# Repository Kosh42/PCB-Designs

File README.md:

# PCB Designs
 A place to share my KiCAD fumblings

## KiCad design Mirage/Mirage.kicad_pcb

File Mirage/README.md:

<p xmlns:cc="http://creativecommons.org/ns#" xmlns:dct="http://purl.org/dc/terms/"><span property="dct:title">Mirage LED Controller</span> by <span property="cc:attributionName">Kosh42EFG</span> is licensed under <a href="http://creativecommons.org/licenses/by/4.0/?ref=chooser-v1" target="_blank" rel="license noopener noreferrer" style="display:inline-block;">Attribution 4.0 International</a></p>

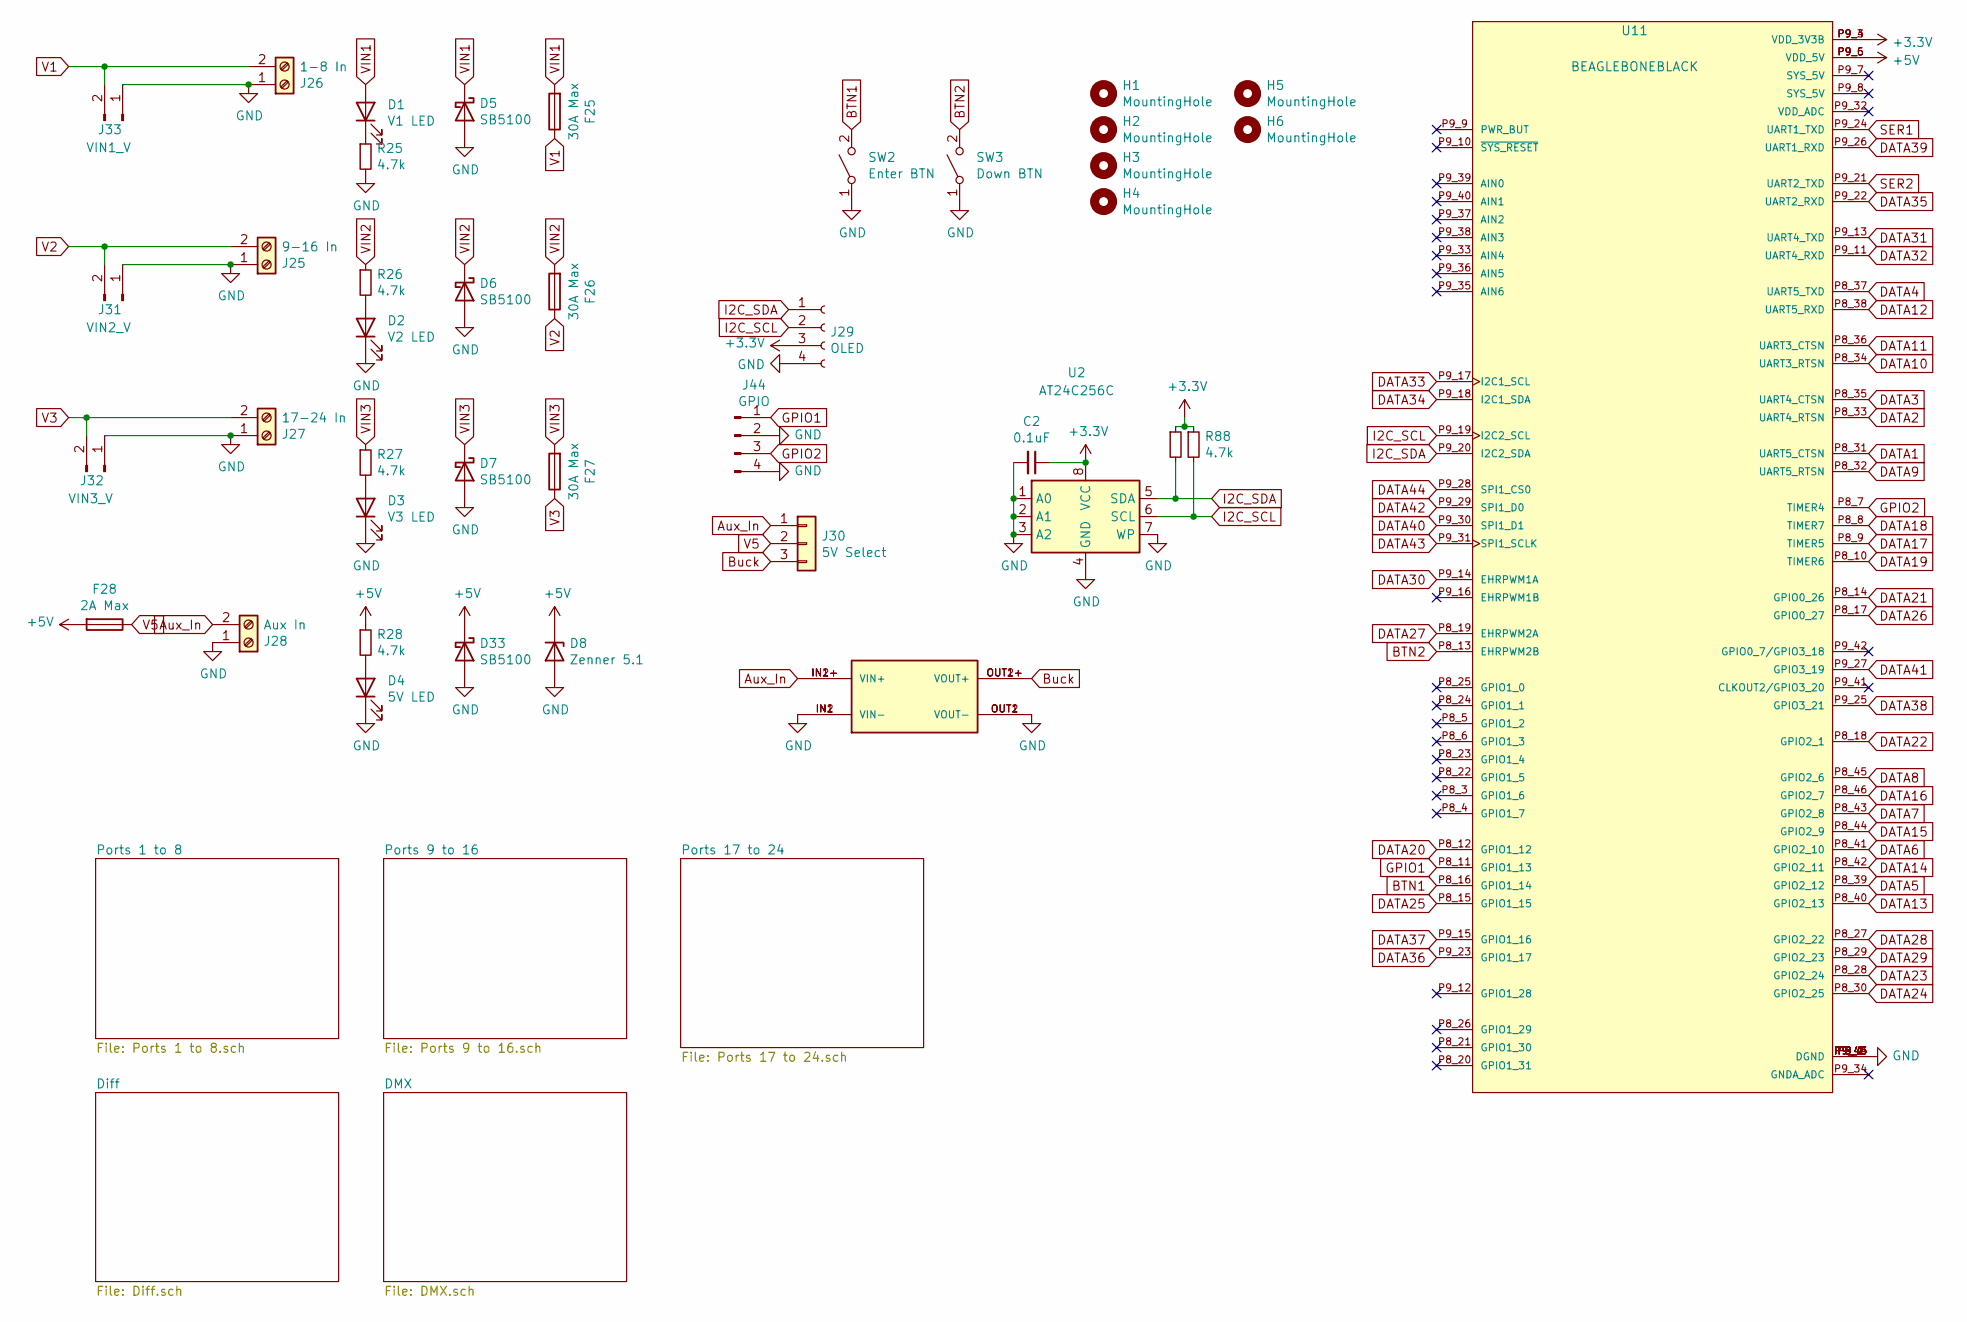
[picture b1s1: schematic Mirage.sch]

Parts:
C2: 0.1uF; C_0805_2012Metric
D1: V1 LED; LED_0603_1608Metric
D2: V2 LED; LED_0603_1608Metric
D3: V3 LED; LED_0603_1608Metric
D4: 5V LED; LED_0603_1608Metric
D5, D6, D7, D33: SB5100; D_DO-201AD_P12.70mm_Horizontal
D8: Zenner 5.1; D_5W_P10.16mm_Horizontal
F25, F26, F27: 30A Max; 3544-2
F28: 2A Max; 3544-2
H1, H2, H3, H4, H5, H6: MountingHole; MountingHole_3.2mm_M3_Pad_TopBottom
J25: 9-16 In; TerminalBlock_MetzConnect_Type701_RT11L02HGLU_1x02_P6.35mm_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
J26: 1-8 In; TerminalBlock_MetzConnect_Type701_RT11L02HGLU_1x02_P6.35mm_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
J27: 17-24 In; TerminalBlock_MetzConnect_Type701_RT11L02HGLU_1x02_P6.35mm_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
J28: Aux In; TerminalBlock_MetzConnect_Type701_RT11L02HGLU_1x02_P6.35mm_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
J29: OLED; PinSocket_1x04_P2.54mm_Vertical
J30: 5V Select; PinHeader_1x03_P2.54mm_Vertical
J31: VIN2_V; JST_XH_B2B-XH-A_1x02_P2.50mm_Vertical
J32: VIN3_V; JST_XH_B2B-XH-A_1x02_P2.50mm_Vertical
J33: VIN1_V; JST_XH_B2B-XH-A_1x02_P2.50mm_Vertical
J44: GPIO; JST_XH_B4B-XH-A_1x04_P2.50mm_Vertical
R25, R26, R27, R28, R29, R88: 4.7k; R_0805_2012Metric
SW2: Enter BTN; SW_PUSH_6mm
SW3: Down BTN; SW_PUSH_6mm
U2: AT24C256C; SOIC-8_3.9x4.9mm_P1.27mm
U10: MP1584; DC-BRICK
U11: BEAGLEBONEBLACK; MODULE_BEAGLEBONEBLACK; PARTREV C

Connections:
+3V3: C2.1, J29.3, R29.1, R88.1, U2.8 (VCC), U11.P9_3 (VDD_3V3B), U11.P9_4 (VDD_3V3B)
+5V: D8.1 (K), D33.1 (K), F28.2, R28.1, U11.P9_5 (VDD_5V), U11.P9_6 (VDD_5V); also elsewhere on the board
Aux_In: J28.2, J30.1, U10.IN1+ (VIN+), U10.IN2+ (VIN+)
BTN1: SW2.2 (B), U11.P8_16 (GPIO1_14)
BTN2: SW3.2 (B), U11.P8_13 (EHRPWM2B)
Buck: J30.3, U10.OUT1+ (VOUT+), U10.OUT2+ (VOUT+)
DATA1: U11.P8_31 (UART5_CTSN); also elsewhere on the board
DATA2: U11.P8_33 (UART4_RTSN); also elsewhere on the board
DATA3: U11.P8_35 (UART4_CTSN); also elsewhere on the board
DATA4: U11.P8_37 (UART5_TXD); also elsewhere on the board
DATA5: U11.P8_39 (GPIO2_12); also elsewhere on the board
DATA6: U11.P8_41 (GPIO2_10); also elsewhere on the board
DATA7: U11.P8_43 (GPIO2_8); also elsewhere on the board
DATA8: U11.P8_45 (GPIO2_6); also elsewhere on the board
DATA9: U11.P8_32 (UART5_RTSN); also elsewhere on the board
DATA10: U11.P8_34 (UART3_RTSN); also elsewhere on the board
DATA11: U11.P8_36 (UART3_CTSN); also elsewhere on the board
DATA12: U11.P8_38 (UART5_RXD); also elsewhere on the board
DATA13: U11.P8_40 (GPIO2_13); also elsewhere on the board
DATA14: U11.P8_42 (GPIO2_11); also elsewhere on the board
DATA15: U11.P8_44 (GPIO2_9); also elsewhere on the board
DATA16: U11.P8_46 (GPIO2_7); also elsewhere on the board
DATA17: U11.P8_9 (TIMER5); also elsewhere on the board
DATA18: U11.P8_8 (TIMER7); also elsewhere on the board
DATA19: U11.P8_10 (TIMER6); also elsewhere on the board
DATA20: U11.P8_12 (GPIO1_12); also elsewhere on the board
DATA21: U11.P8_14 (GPIO0_26); also elsewhere on the board
DATA22: U11.P8_18 (GPIO2_1); also elsewhere on the board
DATA23: U11.P8_28 (GPIO2_24); also elsewhere on the board
DATA24: U11.P8_30 (GPIO2_25); also elsewhere on the board
DATA25: U11.P8_15 (GPIO1_15); also elsewhere on the board
DATA26: U11.P8_17 (GPIO0_27); also elsewhere on the board
DATA27: U11.P8_19 (EHRPWM2A); also elsewhere on the board
DATA28: U11.P8_27 (GPIO2_22); also elsewhere on the board
DATA29: U11.P8_29 (GPIO2_23); also elsewhere on the board
DATA30: U11.P9_14 (EHRPWM1A); also elsewhere on the board
DATA31: U11.P9_13 (UART4_TXD); also elsewhere on the board
DATA32: U11.P9_11 (UART4_RXD); also elsewhere on the board
DATA33: U11.P9_17 (I2C1_SCL); also elsewhere on the board
DATA34: U11.P9_18 (I2C1_SDA); also elsewhere on the board
DATA35: U11.P9_22 (UART2_RXD); also elsewhere on the board
DATA36: U11.P9_23 (GPIO1_17); also elsewhere on the board
DATA37: U11.P9_15 (GPIO1_16); also elsewhere on the board
DATA38: U11.P9_25 (GPIO3_21); also elsewhere on the board
DATA39: U11.P9_26 (UART1_RXD); also elsewhere on the board
DATA40: U11.P9_30 (SPI1_D1); also elsewhere on the board
DATA41: U11.P9_27 (GPIO3_19); also elsewhere on the board
DATA42: U11.P9_29 (SPI1_D0); also elsewhere on the board
DATA43: U11.P9_31 (SPI1_SCLK); also elsewhere on the board
DATA44: U11.P9_28 (SPI1_CS0); also elsewhere on the board
GND: C2.2, D2.1 (K), D3.1 (K), D4.1 (K), D5.2 (A), D6.2 (A), D7.2 (A), D8.2 (A), D33.2 (A), J25.1, J26.1, J27.1, J28.1, J29.4, J31.1, J32.1, J33.1, J44.2, J44.4, R25.2, SW2.1 (A), SW3.1 (A), U2.1 (A0), U2.2 (A1), U2.3 (A2), U2.4 (GND), U2.7 (WP), U10.IN1 (VIN-), U10.IN2 (VIN-), U10.OUT1 (VOUT-), U10.OUT2 (VOUT-), U11.P8_1 (DGND), U11.P8_2 (DGND), U11.P9_1 (DGND), U11.P9_2 (DGND), U11.P9_43 (DGND), U11.P9_44 (DGND), U11.P9_45 (DGND), U11.P9_46 (DGND); also elsewhere on the board
GPIO1: J44.1, U11.P8_11 (GPIO1_13)
GPIO2: J44.3, U11.P8_7 (TIMER4)
I2C_SCL: J29.2, R88.2, U2.6 (SCL), U11.P9_19 (I2C2_SCL)
I2C_SDA: J29.1, R29.2, U2.5 (SDA), U11.P9_20 (I2C2_SDA)
unnamed: D1.1 (K), R25.1
unnamed: D2.2 (A), R26.2
unnamed: D3.2 (A), R27.2
unnamed: D4.2 (A), R28.2
SER1: U11.P9_24 (UART1_TXD); also elsewhere on the board
SER2: U11.P9_21 (UART2_TXD); also elsewhere on the board
V1: F25.1, J26.2, J33.2
V2: F26.1, J25.2, J31.2
V3: F27.1, J27.2, J32.2
V5: F28.1, J30.2
VIN1: D1.2 (A), D5.1 (K), F25.2; also elsewhere on the board
VIN2: D6.1 (K), F26.2, R26.1; also elsewhere on the board
VIN3: D7.1 (K), F27.2, R27.1; also elsewhere on the board

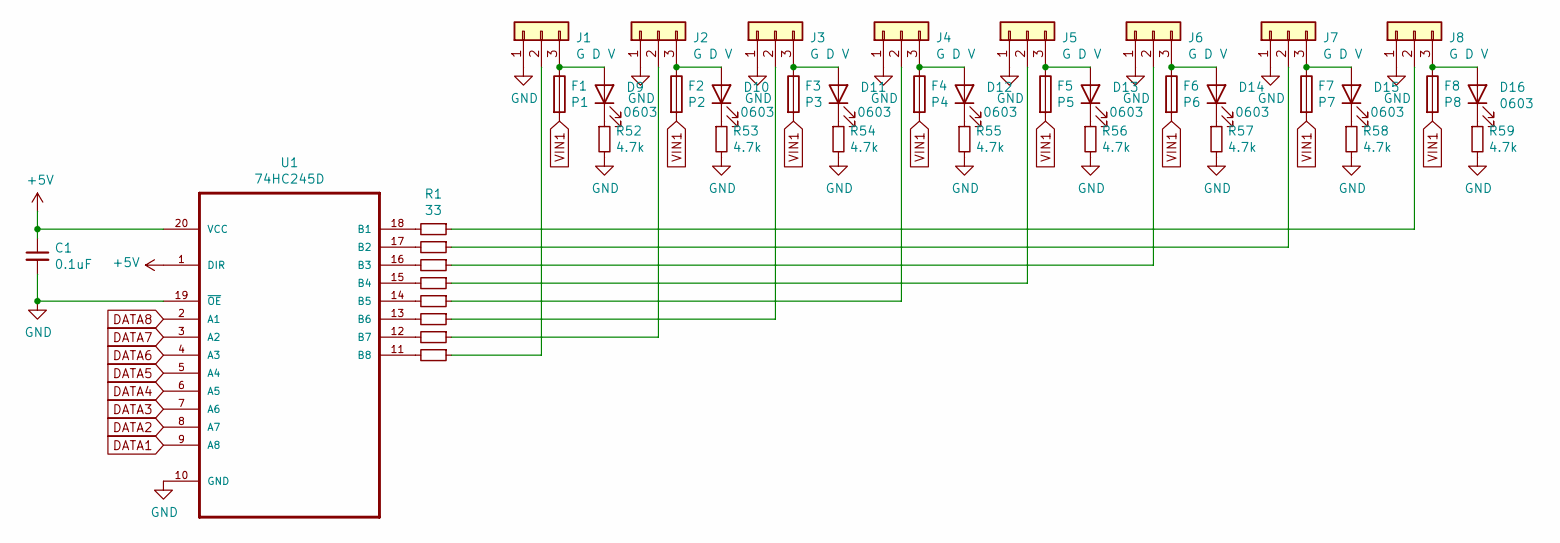
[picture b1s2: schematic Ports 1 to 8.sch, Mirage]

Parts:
C1: 0.1uF; C_0805_2012Metric
D9, D10, D11, D12, D13, D14, D15, D16: 0603; LED_0603_1608Metric
F1: P1; 3544-2
F2: P2; 3544-2
F3: P3; 3544-2
F4: P4; 3544-2
F5: P5; 3544-2
F6: P6; 3544-2
F7: P7; 3544-2
F8: P8; 3544-2
J1, J2, J3, J4, J5, J6, J7, J8: G D V; PhoenixContact_MCV_1,5_3-G-3.5_1x03_P3.50mm_Vertical_Tim
R1, R2, R3, R4, R5, R6, R7, R8: 33; R_0805_2012Metric
R52, R53, R54, R55, R56, R57, R58, R59: 4.7k; R_0805_2012Metric
U1: 74HC245D; SOIC-20W_7.5x12.8mm_P1.27mm

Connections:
+5V: C1.1, U1.1 (DIR), U1.20 (VCC); also elsewhere on the board
DATA1: U1.9 (A8); also elsewhere on the board
DATA2: U1.8 (A7); also elsewhere on the board
DATA3: U1.7 (A6); also elsewhere on the board
DATA4: U1.6 (A5); also elsewhere on the board
DATA5: U1.5 (A4); also elsewhere on the board
DATA6: U1.4 (A3); also elsewhere on the board
DATA7: U1.3 (A2); also elsewhere on the board
DATA8: U1.2 (A1); also elsewhere on the board
GND: C1.2, J1.1, J2.1, J3.1, J4.1, J5.1, J6.1, J7.1, J8.1, R52.2, R53.2, R54.2, R55.2, R56.2, R57.2, R58.2, R59.2, U1.10 (GND), U1.19 (~OE); also elsewhere on the board
unnamed: D9.1 (K), R52.1
unnamed: D9.2 (A), F1.1, J1.3
unnamed: D10.1 (K), R53.1
unnamed: D10.2 (A), F2.1, J2.3
unnamed: D11.1 (K), R54.1
unnamed: D11.2 (A), F3.1, J3.3
unnamed: D12.1 (K), R55.1
unnamed: D12.2 (A), F4.1, J4.3
unnamed: D13.1 (K), R56.1
unnamed: D13.2 (A), F5.1, J5.3
unnamed: D14.1 (K), R57.1
unnamed: D14.2 (A), F6.1, J6.3
unnamed: D15.1 (K), R58.1
unnamed: D15.2 (A), F7.1, J7.3
unnamed: D16.1 (K), R59.1
unnamed: D16.2 (A), F8.1, J8.3
unnamed: J1.2, R8.1
unnamed: J2.2, R7.1
unnamed: J3.2, R6.1
unnamed: J4.2, R5.1
unnamed: J5.2, R4.1
unnamed: J6.2, R3.1
unnamed: J7.2, R2.1
unnamed: J8.2, R1.1
unnamed: R1.2, U1.18 (B1)
unnamed: R2.2, U1.17 (B2)
unnamed: R3.2, U1.16 (B3)
unnamed: R4.2, U1.15 (B4)
unnamed: R5.2, U1.14 (B5)
unnamed: R6.2, U1.13 (B6)
unnamed: R7.2, U1.12 (B7)
unnamed: R8.2, U1.11 (B8)
VIN1: F1.2, F2.2, F3.2, F4.2, F5.2, F6.2, F7.2, F8.2; also elsewhere on the board

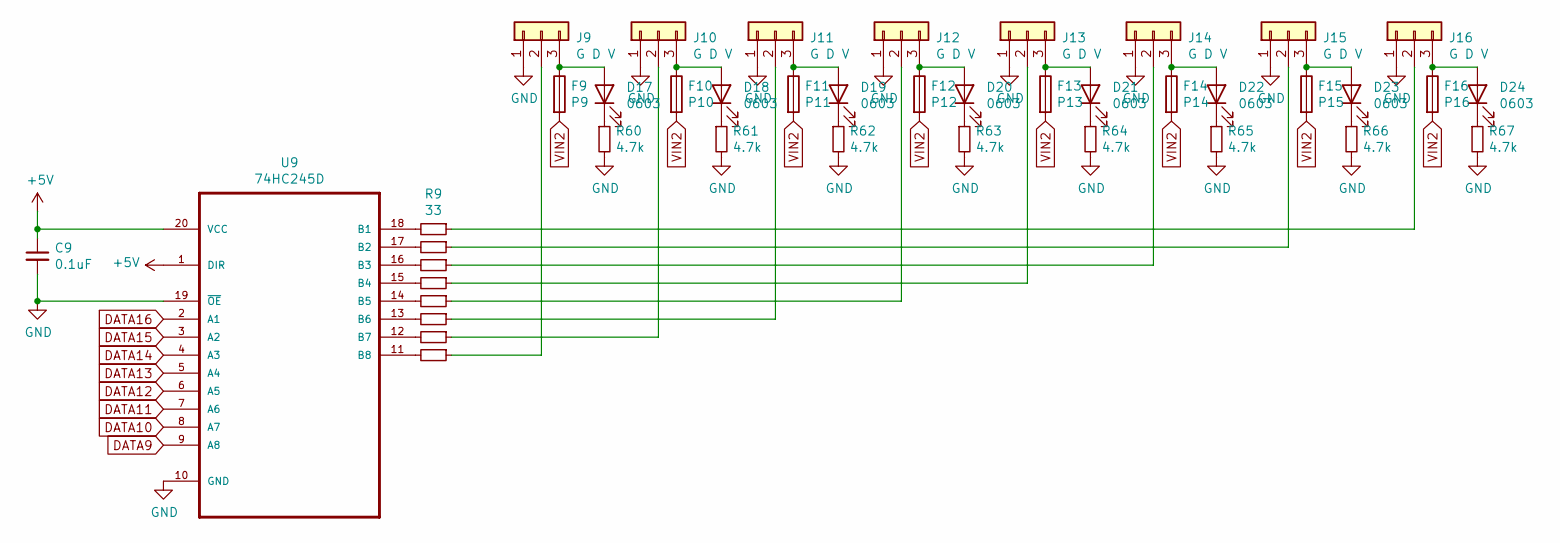
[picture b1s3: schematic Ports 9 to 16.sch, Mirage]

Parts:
C9: 0.1uF; C_0805_2012Metric
D17, D18, D19, D20, D21, D22, D23, D24: 0603; LED_0603_1608Metric
F9: P9; 3544-2
F10: P10; 3544-2
F11: P11; 3544-2
F12: P12; 3544-2
F13: P13; 3544-2
F14: P14; 3544-2
F15: P15; 3544-2
F16: P16; 3544-2
J9, J10, J11, J12, J13, J14, J15, J16: G D V; PhoenixContact_MCV_1,5_3-G-3.5_1x03_P3.50mm_Vertical_Tim
R9, R10, R11, R12, R13, R14, R15, R16: 33; R_0805_2012Metric
R60, R61, R62, R63, R64, R65, R66, R67: 4.7k; R_0805_2012Metric
U9: 74HC245D; SOIC-20W_7.5x12.8mm_P1.27mm

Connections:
+5V: C9.1, U9.1 (DIR), U9.20 (VCC); also elsewhere on the board
DATA9: U9.9 (A8); also elsewhere on the board
DATA10: U9.8 (A7); also elsewhere on the board
DATA11: U9.7 (A6); also elsewhere on the board
DATA12: U9.6 (A5); also elsewhere on the board
DATA13: U9.5 (A4); also elsewhere on the board
DATA14: U9.4 (A3); also elsewhere on the board
DATA15: U9.3 (A2); also elsewhere on the board
DATA16: U9.2 (A1); also elsewhere on the board
GND: C9.2, J9.1, J10.1, J11.1, J12.1, J13.1, J14.1, J15.1, J16.1, R60.2, R61.2, R62.2, R63.2, R64.2, R65.2, R66.2, R67.2, U9.10 (GND), U9.19 (~OE); also elsewhere on the board
unnamed: D17.1 (K), R60.1
unnamed: D17.2 (A), F9.1, J9.3
unnamed: D18.1 (K), R61.1
unnamed: D18.2 (A), F10.1, J10.3
unnamed: D19.1 (K), R62.1
unnamed: D19.2 (A), F11.1, J11.3
unnamed: D20.1 (K), R63.1
unnamed: D20.2 (A), F12.1, J12.3
unnamed: D21.1 (K), R64.1
unnamed: D21.2 (A), F13.1, J13.3
unnamed: D22.1 (K), R65.1
unnamed: D22.2 (A), F14.1, J14.3
unnamed: D23.1 (K), R66.1
unnamed: D23.2 (A), F15.1, J15.3
unnamed: D24.1 (K), R67.1
unnamed: D24.2 (A), F16.1, J16.3
unnamed: J9.2, R16.1
unnamed: J10.2, R15.1
unnamed: J11.2, R14.1
unnamed: J12.2, R13.1
unnamed: J13.2, R12.1
unnamed: J14.2, R11.1
unnamed: J15.2, R10.1
unnamed: J16.2, R9.1
unnamed: R9.2, U9.18 (B1)
unnamed: R10.2, U9.17 (B2)
unnamed: R11.2, U9.16 (B3)
unnamed: R12.2, U9.15 (B4)
unnamed: R13.2, U9.14 (B5)
unnamed: R14.2, U9.13 (B6)
unnamed: R15.2, U9.12 (B7)
unnamed: R16.2, U9.11 (B8)
VIN2: F9.2, F10.2, F11.2, F12.2, F13.2, F14.2, F15.2, F16.2; also elsewhere on the board

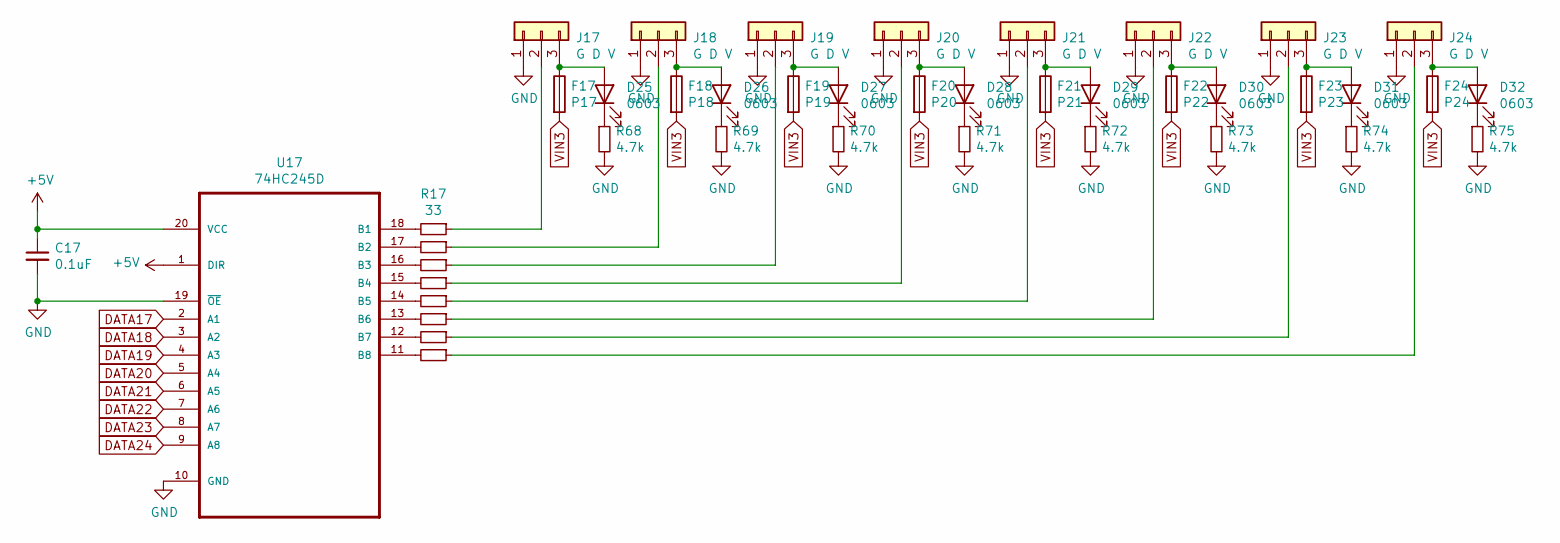
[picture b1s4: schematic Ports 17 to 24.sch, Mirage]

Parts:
C17: 0.1uF; C_0805_2012Metric
D25, D26, D27, D28, D29, D30, D31, D32: 0603; LED_0603_1608Metric
F17: P17; 3544-2
F18: P18; 3544-2
F19: P19; 3544-2
F20: P20; 3544-2
F21: P21; 3544-2
F22: P22; 3544-2
F23: P23; 3544-2
F24: P24; 3544-2
J17, J18, J19, J20, J21, J22, J23, J24: G D V; PhoenixContact_MCV_1,5_3-G-3.5_1x03_P3.50mm_Vertical_Tim
R17, R18, R19, R20, R21, R22, R23, R24: 33; R_0805_2012Metric
R68, R69, R70, R71, R72, R73, R74, R75: 4.7k; R_0805_2012Metric
U17: 74HC245D; SOIC-20W_7.5x12.8mm_P1.27mm

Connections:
+5V: C17.1, U17.1 (DIR), U17.20 (VCC); also elsewhere on the board
DATA17: U17.2 (A1); also elsewhere on the board
DATA18: U17.3 (A2); also elsewhere on the board
DATA19: U17.4 (A3); also elsewhere on the board
DATA20: U17.5 (A4); also elsewhere on the board
DATA21: U17.6 (A5); also elsewhere on the board
DATA22: U17.7 (A6); also elsewhere on the board
DATA23: U17.8 (A7); also elsewhere on the board
DATA24: U17.9 (A8); also elsewhere on the board
GND: C17.2, J17.1, J18.1, J19.1, J20.1, J21.1, J22.1, J23.1, J24.1, R68.2, R69.2, R70.2, R71.2, R72.2, R73.2, R74.2, R75.2, U17.10 (GND), U17.19 (~OE); also elsewhere on the board
unnamed: D25.1 (K), R68.1
unnamed: D25.2 (A), F17.1, J17.3
unnamed: D26.1 (K), R69.1
unnamed: D26.2 (A), F18.1, J18.3
unnamed: D27.1 (K), R70.1
unnamed: D27.2 (A), F19.1, J19.3
unnamed: D28.1 (K), R71.1
unnamed: D28.2 (A), F20.1, J20.3
unnamed: D29.1 (K), R72.1
unnamed: D29.2 (A), F21.1, J21.3
unnamed: D30.1 (K), R73.1
unnamed: D30.2 (A), F22.1, J22.3
unnamed: D31.1 (K), R74.1
unnamed: D31.2 (A), F23.1, J23.3
unnamed: D32.1 (K), R75.1
unnamed: D32.2 (A), F24.1, J24.3
unnamed: J17.2, R17.1
unnamed: J18.2, R18.1
unnamed: J19.2, R19.1
unnamed: J20.2, R20.1
unnamed: J21.2, R21.1
unnamed: J22.2, R22.1
unnamed: J23.2, R23.1
unnamed: J24.2, R24.1
unnamed: R17.2, U17.18 (B1)
unnamed: R18.2, U17.17 (B2)
unnamed: R19.2, U17.16 (B3)
unnamed: R20.2, U17.15 (B4)
unnamed: R21.2, U17.14 (B5)
unnamed: R22.2, U17.13 (B6)
unnamed: R23.2, U17.12 (B7)
unnamed: R24.2, U17.11 (B8)
VIN3: F17.2, F18.2, F19.2, F20.2, F21.2, F22.2, F23.2, F24.2; also elsewhere on the board

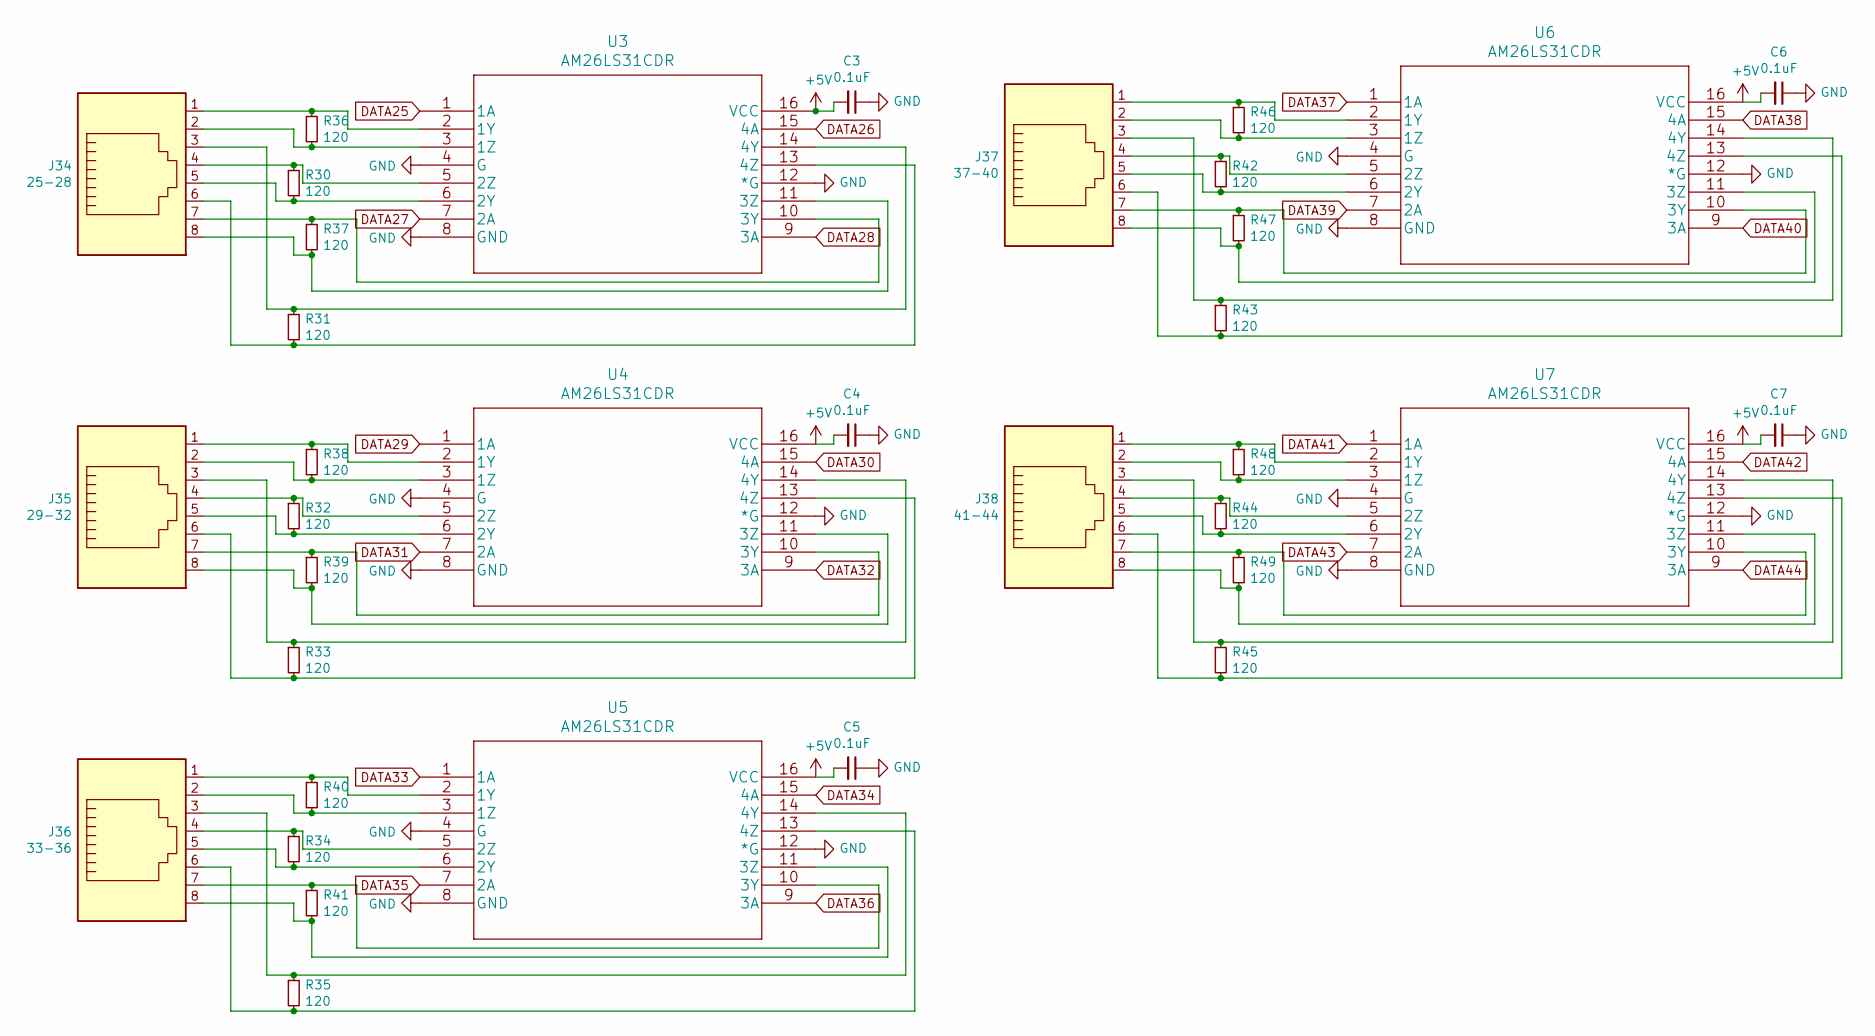
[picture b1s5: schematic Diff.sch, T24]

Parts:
C3, C4, C5, C6, C7: 0.1uF; C_0805_2012Metric
J34: 25-28; RJ45_OST_PJ012-8P8CX_Vertical
J35: 29-32; RJ45_OST_PJ012-8P8CX_Vertical
J36: 33-36; RJ45_OST_PJ012-8P8CX_Vertical
J37: 37-40; RJ45_OST_PJ012-8P8CX_Vertical
J38: 41-44; RJ45_OST_PJ012-8P8CX_Vertical
R30, R31, R32, R33, R34, R35, R36, R37, R38, R39, R40, R41, R42, R43, R44, R45, R46, R47, R48, R49: 120; R_0805_2012Metric
U3, U4, U5, U6, U7: AM26LS31CDR; SOIC-16_3.9x9.9mm_P1.27mm

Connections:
+5V: C3.2, C4.2, C5.2, C6.2, C7.2, U3.16 (VCC), U4.16 (VCC), U5.16 (VCC), U6.16 (VCC), U7.16 (VCC); also elsewhere on the board
DATA25: U3.1 (1A); also elsewhere on the board
DATA26: U3.15 (4A); also elsewhere on the board
DATA27: U3.7 (2A); also elsewhere on the board
DATA28: U3.9 (3A); also elsewhere on the board
DATA29: U4.1 (1A); also elsewhere on the board
DATA30: U4.15 (4A); also elsewhere on the board
DATA31: U4.7 (2A); also elsewhere on the board
DATA32: U4.9 (3A); also elsewhere on the board
DATA33: U5.1 (1A); also elsewhere on the board
DATA34: U5.15 (4A); also elsewhere on the board
DATA35: U5.7 (2A); also elsewhere on the board
DATA36: U5.9 (3A); also elsewhere on the board
DATA37: U6.1 (1A); also elsewhere on the board
DATA38: U6.15 (4A); also elsewhere on the board
DATA39: U6.7 (2A); also elsewhere on the board
DATA40: U6.9 (3A); also elsewhere on the board
DATA41: U7.1 (1A); also elsewhere on the board
DATA42: U7.15 (4A); also elsewhere on the board
DATA43: U7.7 (2A); also elsewhere on the board
DATA44: U7.9 (3A); also elsewhere on the board
GND: C3.1, C4.1, C5.1, C6.1, C7.1, U3.4 (G), U3.8 (GND), U3.12 (*G), U4.4 (G), U4.8 (GND), U4.12 (*G), U5.4 (G), U5.8 (GND), U5.12 (*G), U6.4 (G), U6.8 (GND), U6.12 (*G), U7.4 (G), U7.8 (GND), U7.12 (*G); also elsewhere on the board
unnamed: J34.1, R36.1, U3.2 (1Y)
unnamed: J34.2, R36.2, U3.3 (1Z)
unnamed: J34.3, R31.1, U3.14 (4Y)
unnamed: J34.4, R30.1, U3.5 (2Z)
unnamed: J34.5, R30.2, U3.6 (2Y)
unnamed: J34.6, R31.2, U3.13 (4Z)
unnamed: J34.7, R37.1, U3.10 (3Y)
unnamed: J34.8, R37.2, U3.11 (3Z)
unnamed: J35.1, R38.1, U4.2 (1Y)
unnamed: J35.2, R38.2, U4.3 (1Z)
unnamed: J35.3, R33.1, U4.14 (4Y)
unnamed: J35.4, R32.1, U4.5 (2Z)
unnamed: J35.5, R32.2, U4.6 (2Y)
unnamed: J35.6, R33.2, U4.13 (4Z)
unnamed: J35.7, R39.1, U4.10 (3Y)
unnamed: J35.8, R39.2, U4.11 (3Z)
unnamed: J36.1, R40.1, U5.2 (1Y)
unnamed: J36.2, R40.2, U5.3 (1Z)
unnamed: J36.3, R35.1, U5.14 (4Y)
unnamed: J36.4, R34.1, U5.5 (2Z)
unnamed: J36.5, R34.2, U5.6 (2Y)
unnamed: J36.6, R35.2, U5.13 (4Z)
unnamed: J36.7, R41.1, U5.10 (3Y)
unnamed: J36.8, R41.2, U5.11 (3Z)
unnamed: J37.1, R46.1, U6.2 (1Y)
unnamed: J37.2, R46.2, U6.3 (1Z)
unnamed: J37.3, R43.1, U6.14 (4Y)
unnamed: J37.4, R42.1, U6.5 (2Z)
unnamed: J37.5, R42.2, U6.6 (2Y)
unnamed: J37.6, R43.2, U6.13 (4Z)
unnamed: J37.7, R47.1, U6.10 (3Y)
unnamed: J37.8, R47.2, U6.11 (3Z)
unnamed: J38.1, R48.1, U7.2 (1Y)
unnamed: J38.2, R48.2, U7.3 (1Z)
unnamed: J38.3, R45.1, U7.14 (4Y)
unnamed: J38.4, R44.1, U7.5 (2Z)
unnamed: J38.5, R44.2, U7.6 (2Y)
unnamed: J38.6, R45.2, U7.13 (4Z)
unnamed: J38.7, R49.1, U7.10 (3Y)
unnamed: J38.8, R49.2, U7.11 (3Z)

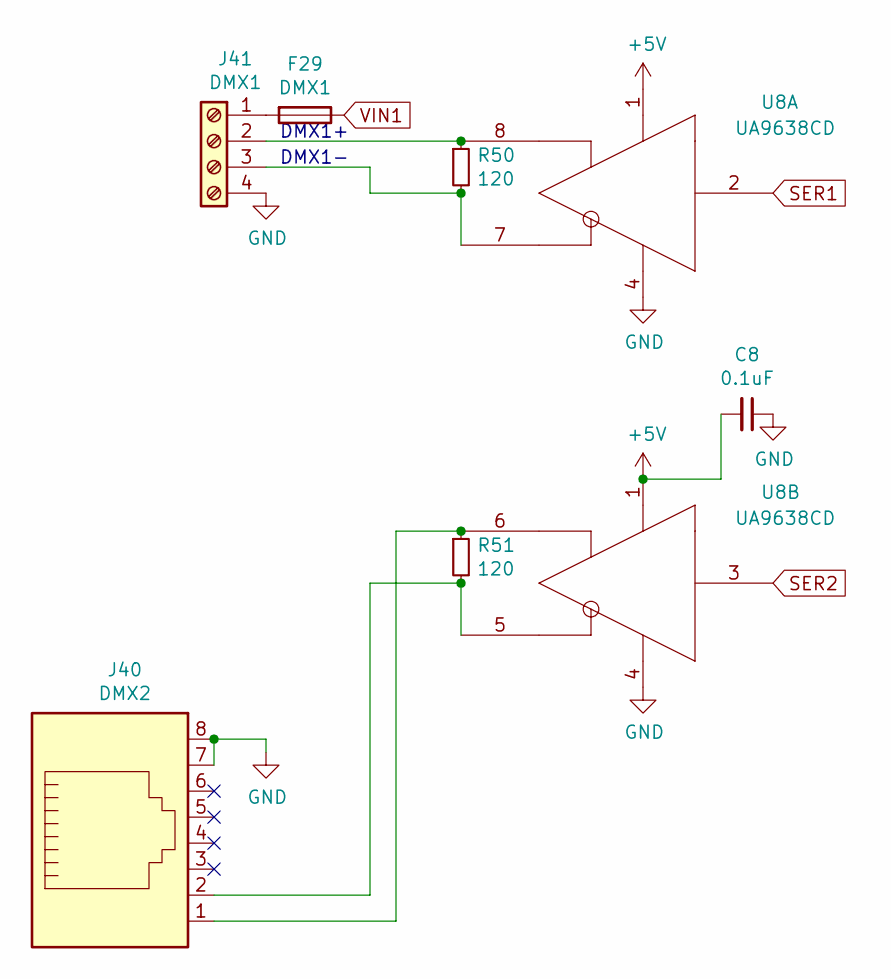
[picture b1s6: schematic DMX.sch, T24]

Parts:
C8: 0.1uF; C_0805_2012Metric
F29: DMX1; 3544-2
J40: DMX2; RJ45_OST_PJ012-8P8CX_Vertical
J41: DMX1; PhoenixContact_MCV_1,5_4-G-3.5_1x04_P3.50mm_Vertical
R50, R51: 120; R_0805_2012Metric
U8: UA9638CD; SOIC-8_3.9x4.9mm_P1.27mm

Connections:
+5V: C8.2, U8.1 (VCC); also elsewhere on the board
GND: C8.1, J40.7, J40.8, J41.4, U8.4 (GND); also elsewhere on the board
unnamed: F29.2, J41.1
unnamed: J40.1, R51.1, U8.6 (OUTB)
unnamed: J40.2, R51.2, U8.5 (OUTA)
unnamed: J41.2, R50.1, U8.8 (OUTB)
unnamed: J41.3, R50.2, U8.7 (OUTA)
SER1: U8.2 (IN); also elsewhere on the board
SER2: U8.3 (IN); also elsewhere on the board
VIN1: F29.1; also elsewhere on the board

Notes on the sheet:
DMX1+
DMX1-

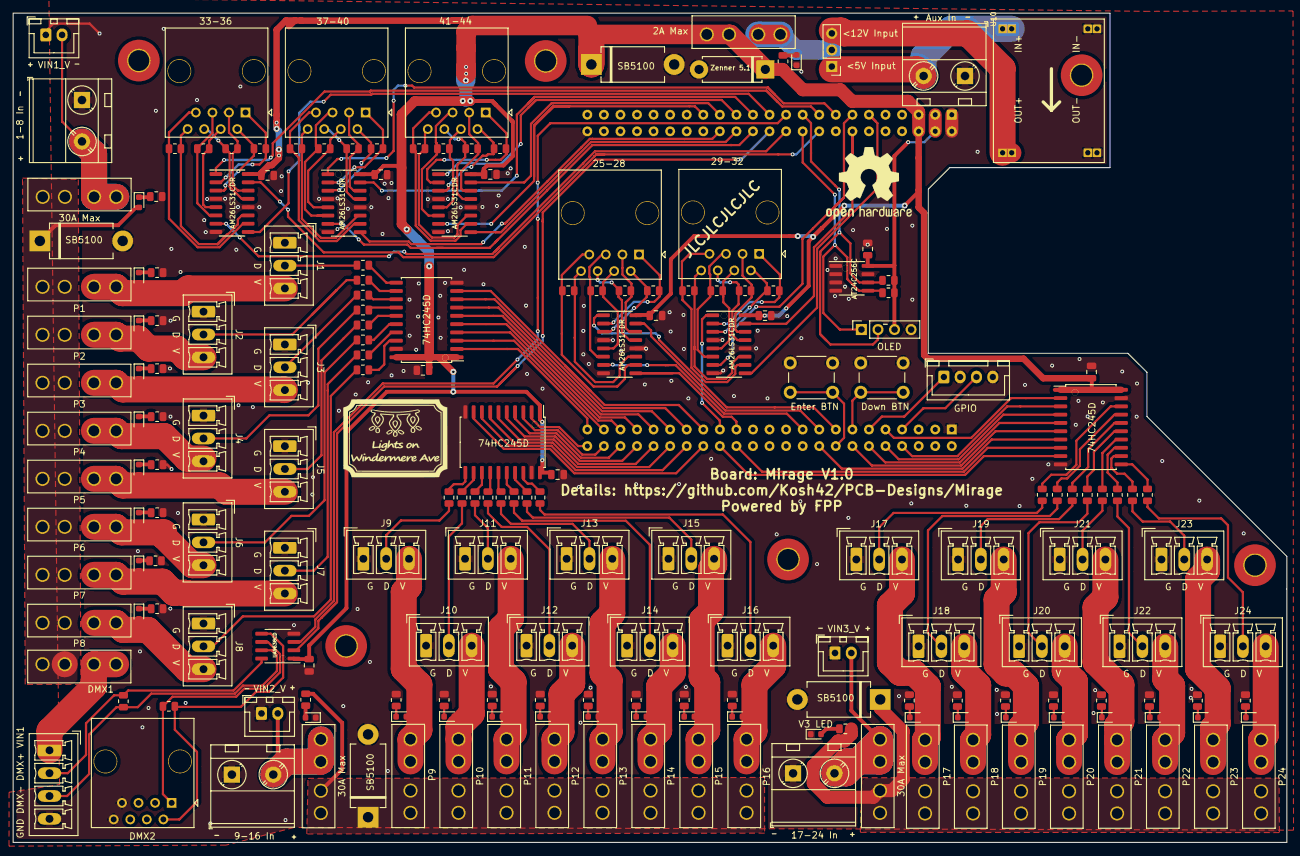
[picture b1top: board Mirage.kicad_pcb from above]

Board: 2 copper layers, 195.3 x 127.1 mm, 209 parts (0 on the bottom side), 209 nets.

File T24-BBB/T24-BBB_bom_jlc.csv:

"Comment","Designator","Footprint","LCSC Part #"
"0.1uF","C2,C1,C9,C17,C3,C4,C5,C7,C6,C8","C_0805_2012Metric","C49678"
"V1 LED","D1","LED_0603_1608Metric","C72043"
"V2 LED","D2","LED_0603_1608Metric","C72043"
"V3 LED","D3","LED_0603_1608Metric","C72043"
"5V LED","D4","LED_0603_1608Metric","C72043"
"0603","D16,D15,D14,D13,D12,D11,D10,D9,D24,D23,D22,D21,D20,D19,D18,D17,D32,D31,D30,D29,D28,D27,D26,D25","LED_0603_1608Metric","C72043"
"33","R1,R2,R3,R4,R5,R6,R7,R8,R9,R10,R11,R12,R13,R14,R15,R16,R17,R18,R19,R20,R21,R22,R23,R24","R_0805_2012Metric","C17634"
"4.7k","R25,R26,R28,R27,R88,R29,R59,R58,R57,R56,R55,R54,R53,R52,R67,R66,R65,R64,R63,R62,R61,R60,R75,R74,R73,R72,R71,R70,R69,R68","R_0805_2012Metric","C17673"
"120","R30,R36,R37,R31,R32,R38,R39,R33,R34,R40,R41,R35,R42,R46,R47,R43,R44,R48,R49,R45,R50,R51","R_0805_2012Metric","C17437"
"74HC245D","U1,U9,U17","SOIC-20W_7.5x12.8mm_P1.27mm","C5625"
"AT24C256C","U2","SOIC-8_3.9x4.9mm_P1.27mm","C6482"
"AM26LS31CDR","U3,U4,U5,U6,U7","SOIC-16_3.9x9.9mm_P1.27mm","C6179"
"UA9638CD","U8","SOIC-8_3.9x4.9mm_P1.27mm","C435812"

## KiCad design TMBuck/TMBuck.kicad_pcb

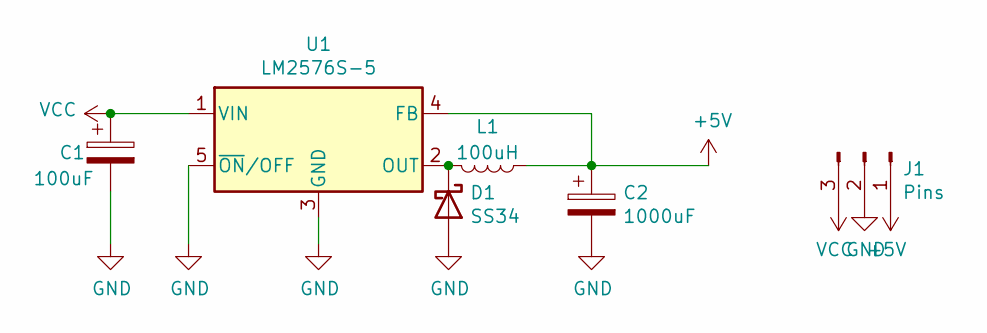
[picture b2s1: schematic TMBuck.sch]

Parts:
C1: 100uF; CP_Radial_D5.0mm_P2.00mm
C2: 1000uF; CP_Radial_D10.0mm_P5.00mm
D1: SS34; D_SMA; LCSC C8678
J1: Pins; PinHeader_1x03_P2.54mm_Horizontal
L1: 100uH; L_0805_2012Metric; LCSC C68035
U1: LM2576S-5; TO-263-5_TabPin3; LCSC C340927

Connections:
+5V: C2.1, J1.1, L1.1, U1.4 (FB)
GND: C1.2, C2.2, D1.2 (A), J1.2, U1.3 (GND), U1.5 (~ON~/OFF)
unnamed: D1.1 (K), L1.2, U1.2 (OUT)
VCC: C1.1, J1.3, U1.1 (VIN)

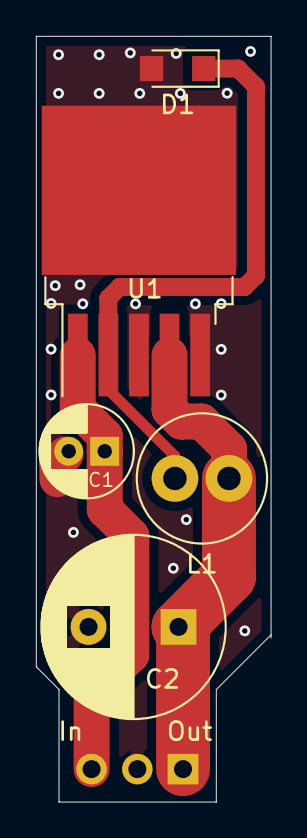
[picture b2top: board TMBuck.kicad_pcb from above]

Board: 2 copper layers, 13.0 x 42.5 mm, 6 parts (1 on the bottom side), 4 nets.

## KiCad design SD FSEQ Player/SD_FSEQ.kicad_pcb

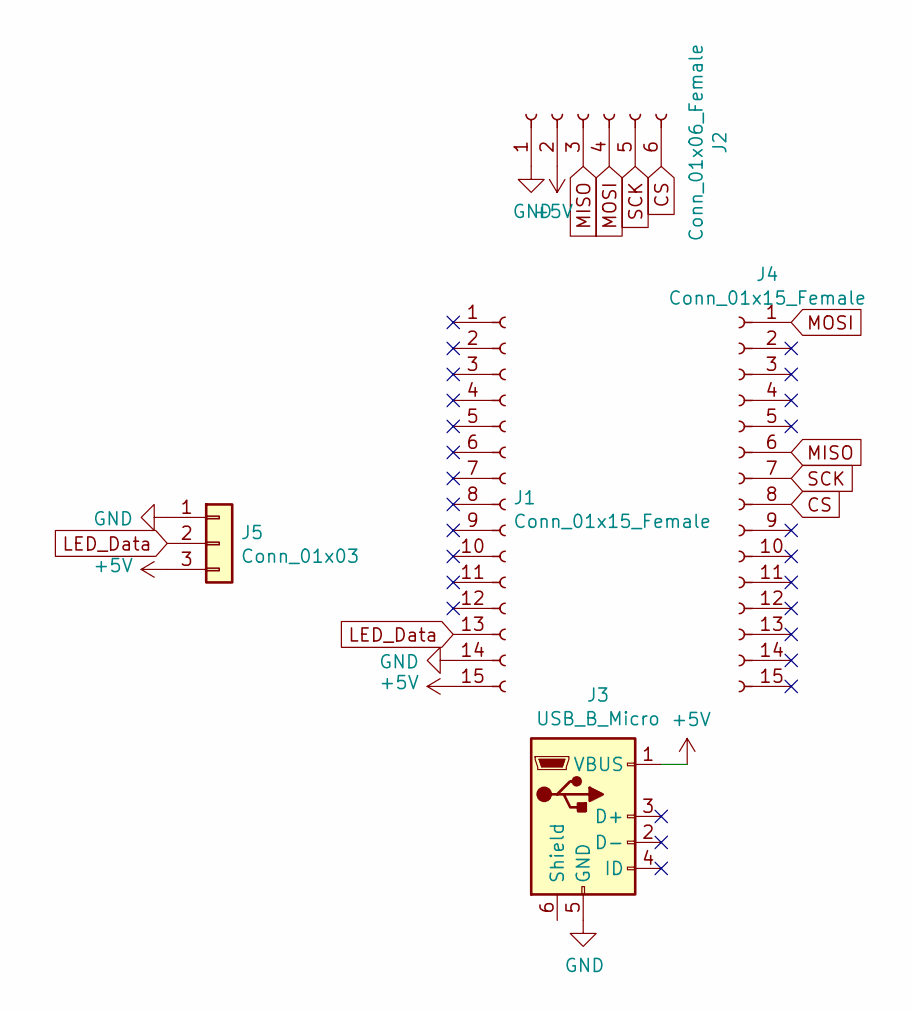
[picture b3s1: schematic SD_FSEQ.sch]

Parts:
J1, J4: Conn_01x15_Female; PinSocket_1x15_P2.54mm_Vertical
J2: Conn_01x06_Female; PinSocket_1x06_P2.54mm_Horizontal
J3: USB_B_Micro; USB_Micro-B_Wuerth_629105150521
J5: Conn_01x03; PhoenixContact_MCV_1,5_3-G-3.5_1x03_P3.50mm_Vertical

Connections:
+5V: J1.15, J2.2, J3.1 (VBUS), J5.3
CS: J2.6, J4.8
GND: J1.14, J2.1, J3.5 (GND), J5.1
LED_Data: J1.13, J5.2
MISO: J2.3, J4.6
MOSI: J2.4, J4.1
SCK: J2.5, J4.7

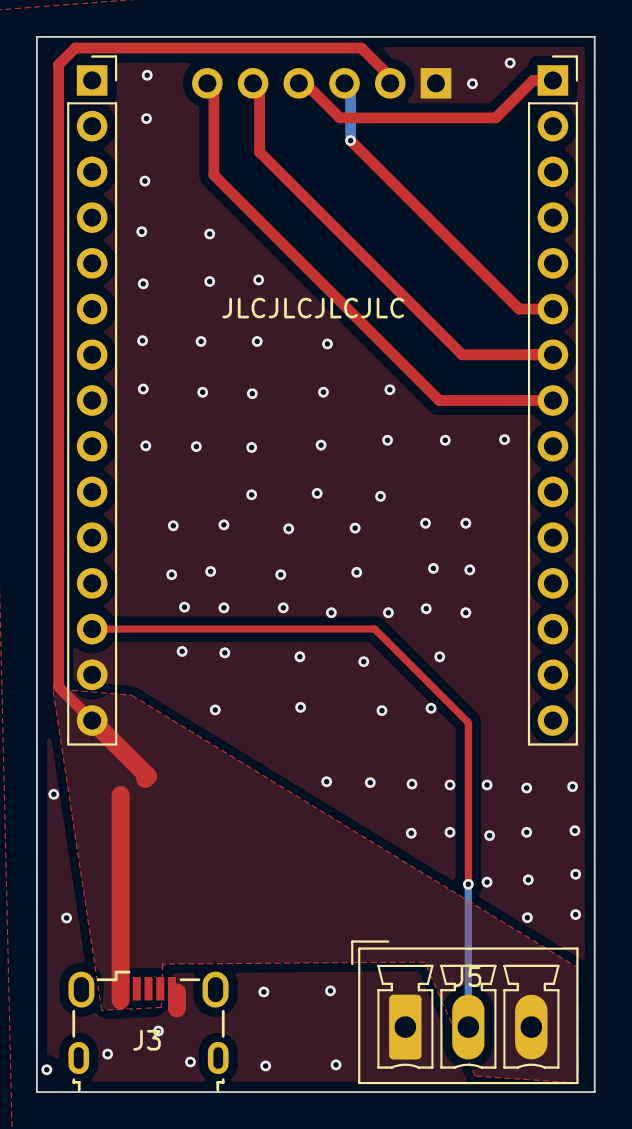
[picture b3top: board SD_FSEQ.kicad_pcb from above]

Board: 2 copper layers, 31.0 x 58.6 mm, 5 parts (1 on the bottom side), 7 nets.

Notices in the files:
parts and their libraries:
Copyright 2016 Accelerated Designs. All rights reserved.
